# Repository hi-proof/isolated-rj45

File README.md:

# Rev B changes

- Using non-magnetic RJ45 connector

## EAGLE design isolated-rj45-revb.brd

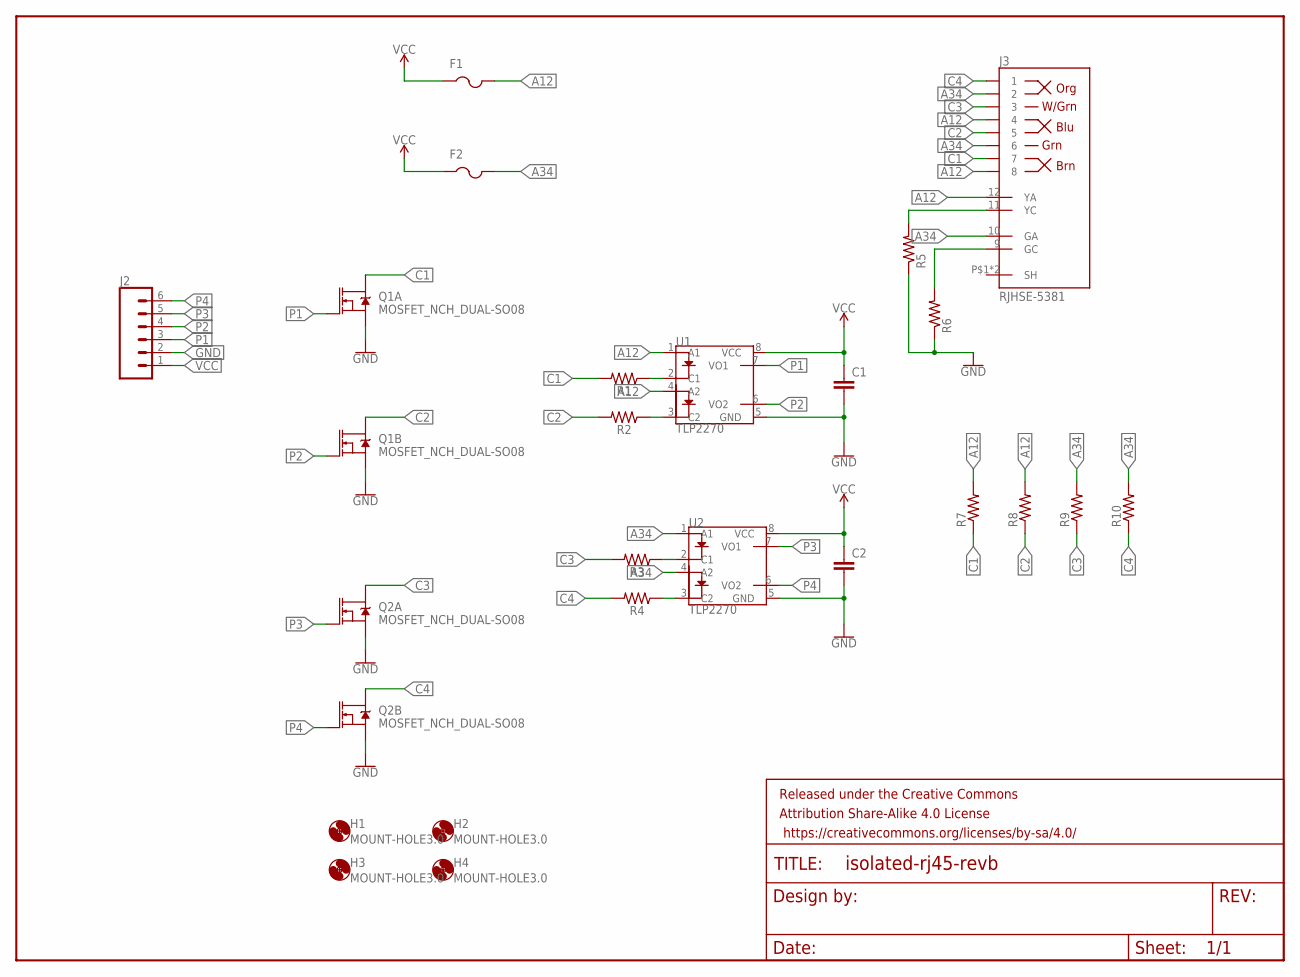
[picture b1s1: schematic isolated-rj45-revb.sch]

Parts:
C1, C2: CAPACITOR_0603_L; RESC0603_L
F1, F2: PTCFUSE-1206; R1206
FRAME1: FRAME-LETTERNO_PACKAGE; DUMMY
H1, H2, H3, H4: MOUNT-HOLE3.0; 3,0
J2: CONN_06SILK_FEMALE_PTH; 1X06
J3: RJHSE-5381; RJHSE-538X
Q1, Q2: MOSFET_NCH_DUAL-SO08; SO08
R1, R2, R3, R4: 0603
R5, R6, R7, R8, R9, R10: R-US_R0603; R0603
U1, U2: TLP2270; 11-6B1A

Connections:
A12: F1.2, J3.4, J3.8, J3.12 (YA), R7.2, R8.2, U1.1 (A1), U1.4 (A2)
A34: F2.2, J3.2, J3.6, J3.10 (GA), R9.2, R10.2, U2.1 (A1), U2.4 (A2)
C1: J3.7, Q1.7 (D), Q1.8 (D), R1.2, R7.1
C2: J3.5, Q1.5 (D), Q1.6 (D), R2.2, R8.1
C3: J3.3, Q2.7 (D), Q2.8 (D), R3.2, R9.1
C4: J3.1, Q2.5 (D), Q2.6 (D), R4.2, R10.1
GND: C1.2, C2.2, J2.2, Q1.1 (S), Q1.3 (S), Q2.1 (S), Q2.3 (S), R5.1, R6.1, U1.5 (GND), U2.5 (GND)
unnamed: R1.1, U1.2 (C1)
unnamed: R2.1, U1.3 (C2)
unnamed: R3.1, U2.2 (C1)
unnamed: R4.1, U2.3 (C2)
unnamed: J3.11 (YC), R5.2
unnamed: J3.9 (GC), R6.2
P1: J2.3, Q1.2 (G), U1.7 (VO1)
P2: J2.4, Q1.4 (G), U1.6 (VO2)
P3: J2.5, Q2.2 (G), U2.7 (VO1)
P4: J2.6, Q2.4 (G), U2.6 (VO2)
VCC: C1.1, C2.1, F1.1, F2.1, J2.1, U1.8 (VCC), U2.8 (VCC)

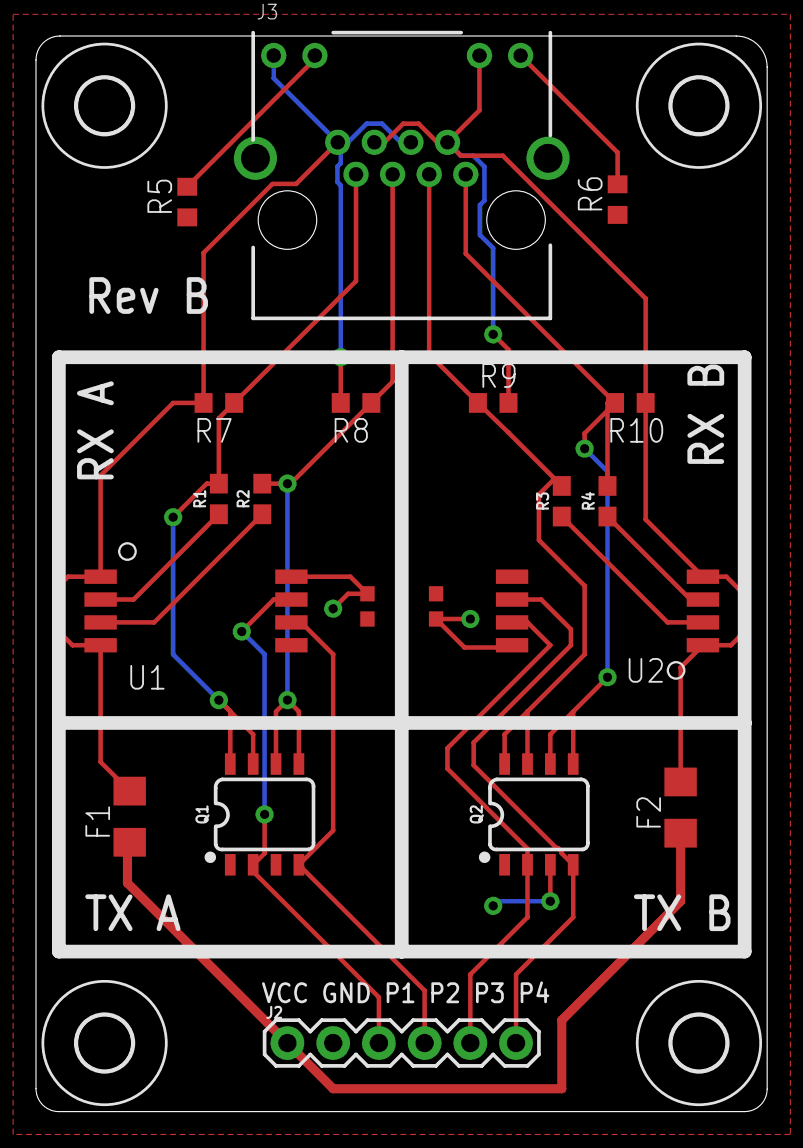
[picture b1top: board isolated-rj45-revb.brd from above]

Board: 2 copper layers, 40.6 x 59.8 mm, 25 parts (0 on the bottom side), 18 nets.

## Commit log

2019-11-04 Updated readme for rev b
2019-11-04 Updated silkscreen for rev b

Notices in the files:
parts and their libraries:
SparkFun-DiscreteSemi: Licensing: Creative Commons ShareAlike 4.0 International - https://creativecommons.org/licenses/by-sa/4.0
SparkFun-Aesthetics: Released under the Creative Commons Attribution Share-Alike 4.0 License
SparkFun-Aesthetics: https://creativecommons.org/licenses/by-sa/4.0
